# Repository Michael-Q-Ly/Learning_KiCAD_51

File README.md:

# Learning KiCAD 5.1

This repo is made for me to learn how to make my own PCBs using KiCAD 5.1

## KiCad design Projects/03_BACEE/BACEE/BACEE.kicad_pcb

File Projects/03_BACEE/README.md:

# Project 3: BACEE
- - - -
This repository contains the PCB design project from the book and course "[Kicad Like a Pro](https://techexplorations.com/so/kicada/)"

This project implements an Arduino-compatible board mostly using SMD components, and
I will be following Dr. Peter Dalmaris' online instruction to design this board.

The board will contain a micro controller, two EEPROM modules, a clock and calendar
module, two crystal oscillators, and several SMD-sized resistors, capacitors and LEDs.
In addition, it will include headers for connecting peripherals to the micro controller.

The name given to this board is BACEE because it is a "Battery-powered Arduino
with Clock and Extended EEPROM."

This project will combine concepts I learned from the previous two projects

## Learning Objectives
- - - -
1. [x] Explore Kicad's more powerful features such as splitting schematic diagrams into more than one sheet
2. [x] Use an external autorouter
3. [x] Convert a two-layer board into a four-layer board

### How to use the FreeRouting with LayoutEditor
To use [FreeRouting](https://freerouting.org/), you may choose to install it by itself, or with LayoutEditor, which comes with FreeRouting. I chose to install LayoutEditor.

To use FreeRouting, I copied the *freeRouting.jar* file into my project directory. I then exported a spectra design file from Kicad's Pcbnew window.
Next, I ran the following in the command line, (make sure you are referring to the correct directory!):

	$java -jar freeRouting.jar

This opened up a new window to allow me to select the spectra design file. I chose whichever spectra file I needed, and then ran autorouting.

After autorouting finished, I simply imported the spectra session into Pcbnew and verified the routing using a DRC.
That's it!

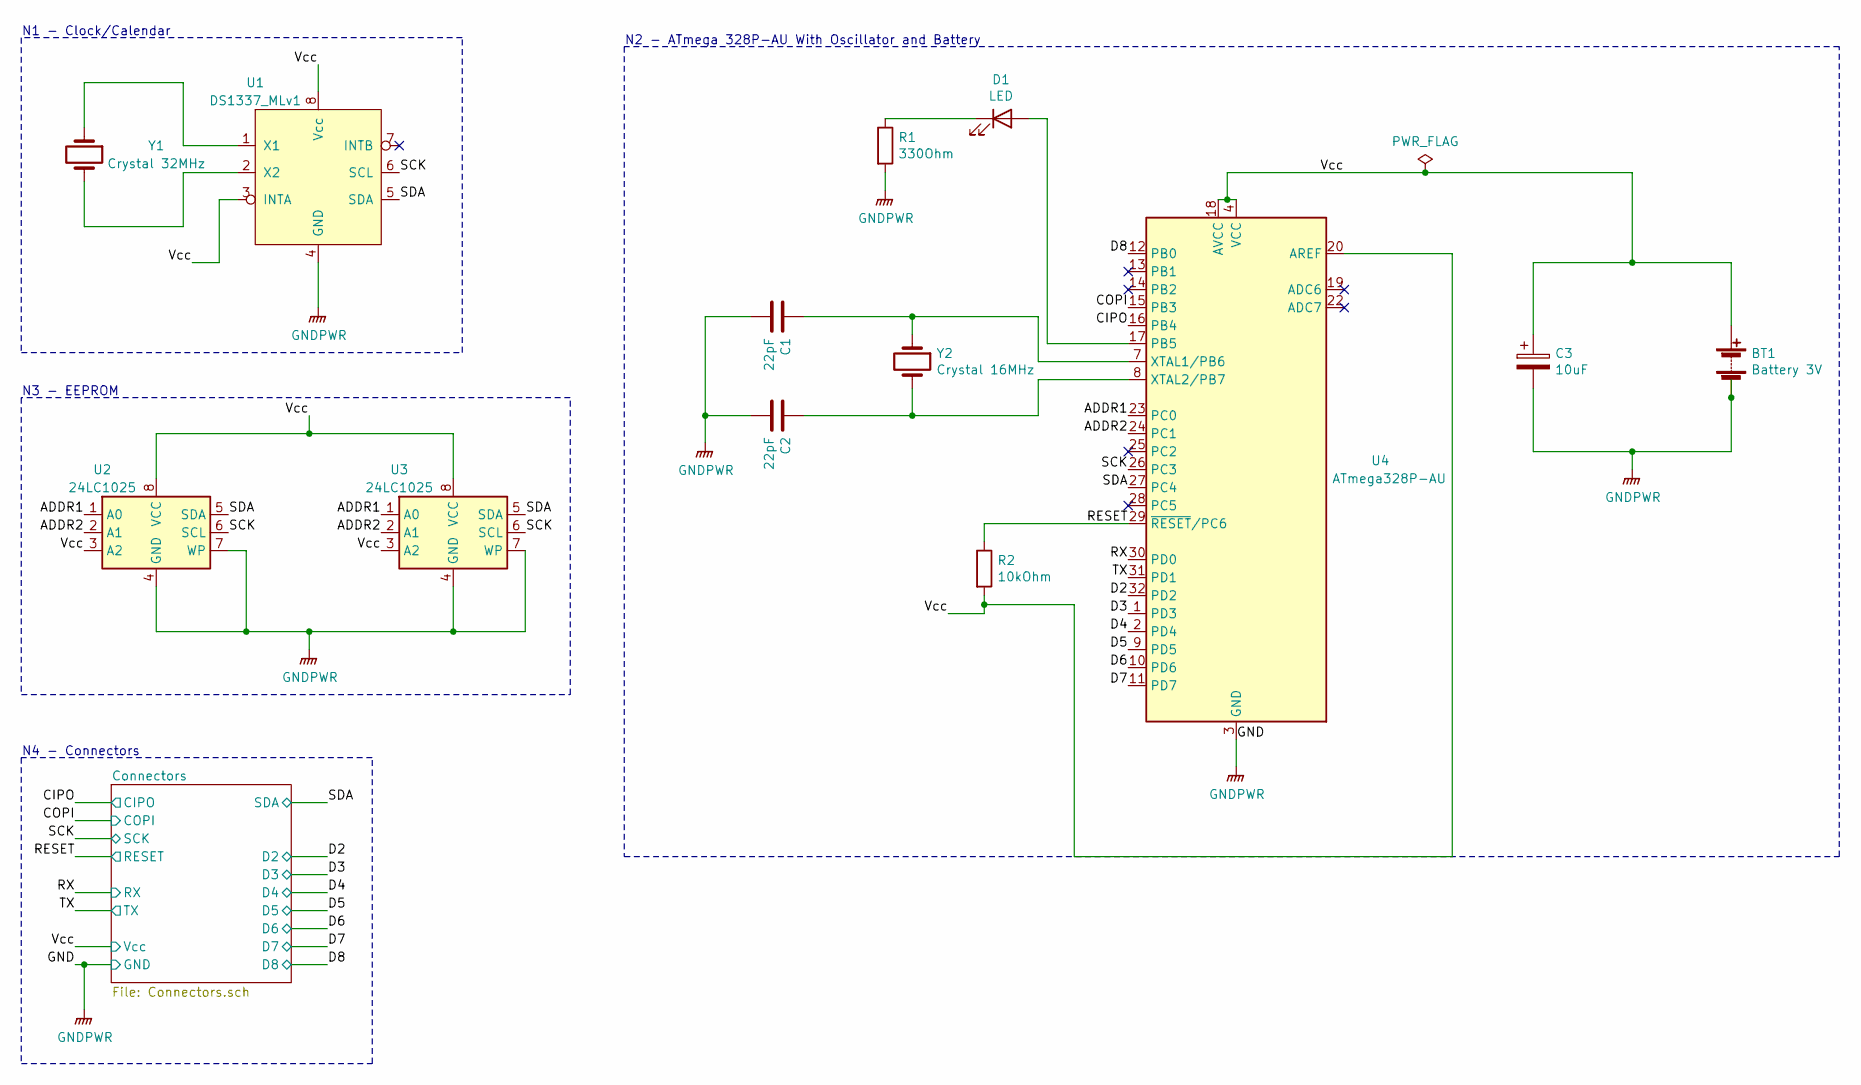
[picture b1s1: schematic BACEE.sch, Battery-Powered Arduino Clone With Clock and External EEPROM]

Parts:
BT1: Battery 3V; PinHeader_1x02_P2.54mm_Vertical
C1, C2: 22pF; D_0805_2012Metric_Pad1.15x1.40mm_HandSolder
C3: 10uF; D_0805_2012Metric_Pad1.15x1.40mm_HandSolder
D1: LED; LED_0805_2012Metric_Pad1.15x1.40mm_HandSolder
R1: 330Ohm; R_0805_2012Metric_Pad1.20x1.40mm_HandSolder
R2: 10kOhm; R_0805_2012Metric_Pad1.20x1.40mm_HandSolder
U1: DS1337_MLv1; SO-8_5.3x6.2mm_P1.27mm
U2, U3: 24LC1025; SOIJ-8_5.3x5.3mm_P1.27mm
U4: ATmega328P-AU; TQFP-32_7x7mm_P0.8mm
Y1: Crystal 32MHz; Crystal_SMD_MicroCrystal_CC7V-T1A-2Pin_3.2x1.5mm
Y2: Crystal 16MHz; Crystal_SMD_5032-2Pin_5.0x3.2mm_HandSoldering

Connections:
/ADDR1: U2.1 (A0), U3.1 (A0), U4.23 (PC0)
/ADDR2: U2.2 (A1), U3.2 (A1), U4.24 (PC1)
/CIPO: U4.16 (PB4); also elsewhere on the board
/COPI: U4.15 (PB3); also elsewhere on the board
/D2: U4.32 (PD2); also elsewhere on the board
/D3: U4.1 (PD3); also elsewhere on the board
/D4: U4.2 (PD4); also elsewhere on the board
/D5: U4.9 (PD5); also elsewhere on the board
/D6: U4.10 (PD6); also elsewhere on the board
/D7: U4.11 (PD7); also elsewhere on the board
/D8: U4.12 (PB0); also elsewhere on the board
/RESET: R2.1, U4.29 (~RESET~/PC6); also elsewhere on the board
/RX: U4.30 (PD0); also elsewhere on the board
/SCK: U1.6 (SCL), U2.6 (SCL), U3.6 (SCL), U4.26 (PC3); also elsewhere on the board
/SDA: U1.5 (SDA), U2.5 (SDA), U3.5 (SDA), U4.27 (PC4); also elsewhere on the board
/TX: U4.31 (PD1); also elsewhere on the board
/Vcc: BT1.1 (+), C3.1, R2.2, U1.3 (INTA), U1.8 (Vcc), U2.3 (A2), U2.8 (VCC), U3.3 (A2), U3.8 (VCC), U4.4 (VCC), U4.6 (VCC), U4.18 (AVCC), U4.20 (AREF); also elsewhere on the board
GNDPWR: BT1.2 (-), C1.2, C2.2, C3.2, R1.2, U1.4 (GND), U2.4 (GND), U2.7 (WP), U3.4 (GND), U3.7 (WP), U4.3 (GND), U4.5 (GND), U4.21 (GND); also elsewhere on the board
unnamed: C1.1, U4.7 (XTAL1/PB6), Y2.1
unnamed: C2.1, U4.8 (XTAL2/PB7), Y2.2
unnamed: D1.1 (K), R1.1
unnamed: D1.2 (A), U4.17 (PB5)
unnamed: U1.1 (X1), Y1.1
unnamed: U1.2 (X2), Y1.2

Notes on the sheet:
N1 - Clock/Calendar
N3 - EEPROM
N2 - ATmega 328P-AU With Oscillator and Battery
N4 - Connectors

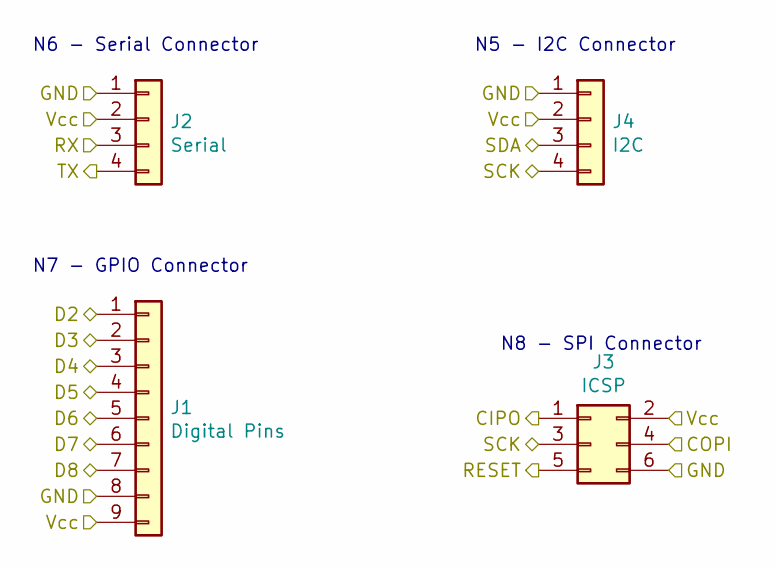
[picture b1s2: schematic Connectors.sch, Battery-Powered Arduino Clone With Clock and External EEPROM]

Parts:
J1: Digital Pins; PinSocket_1x09_P2.54mm_Vertical
J2: Serial; PinSocket_1x04_P2.54mm_Vertical
J3: ICSP; PinSocket_2x03_P2.54mm_Vertical
J4: I2C; PinSocket_1x04_P2.54mm_Vertical

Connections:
/CIPO: J3.1; also elsewhere on the board
/COPI: J3.4; also elsewhere on the board
/D2: J1.1; also elsewhere on the board
/D3: J1.2; also elsewhere on the board
/D4: J1.3; also elsewhere on the board
/D5: J1.4; also elsewhere on the board
/D6: J1.5; also elsewhere on the board
/D7: J1.6; also elsewhere on the board
/D8: J1.7; also elsewhere on the board
/RESET: J3.5; also elsewhere on the board
/RX: J2.3; also elsewhere on the board
/SCK: J3.3, J4.4; also elsewhere on the board
/SDA: J4.3; also elsewhere on the board
/TX: J2.4; also elsewhere on the board
/Vcc: J1.9, J2.2, J3.2, J4.2; also elsewhere on the board
GNDPWR: J1.8, J2.1, J3.6, J4.1; also elsewhere on the board

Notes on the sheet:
N6 - Serial Connector
N5 - I2C Connector
N7 - GPIO Connector
N8 - SPI Connector

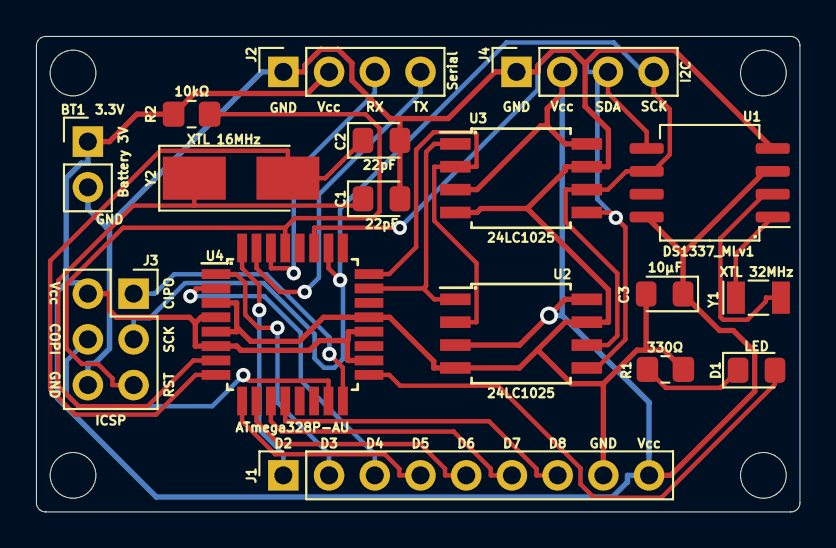
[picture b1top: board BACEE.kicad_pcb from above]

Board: 2 copper layers, 42.4 x 26.4 mm, 17 parts (0 on the bottom side), 24 nets.

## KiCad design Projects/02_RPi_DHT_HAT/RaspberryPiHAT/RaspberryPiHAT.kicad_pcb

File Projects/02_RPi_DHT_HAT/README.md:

# Project 2: Raspberry Pi Full Stack HAT
- - - -
This repository contains the PCB design project from the book and course "[Kicad Like a Pro](https://techexplorations.com/so/kicada/)"

this project implements a Raspberry Pi HAT for a DHT22 temperature and humidity sensor.

## Learning Objectives
- - - -
1. [x] Add surface-mounted devices (SMD) to your board
2. [x] Minimize the amount of space needed for a board
3. [x] Create non-rectangular shapes for the board outline
4. [x] Add mounting holes
5. [x] Revice the board outline after you place the footprints in order to conserve space

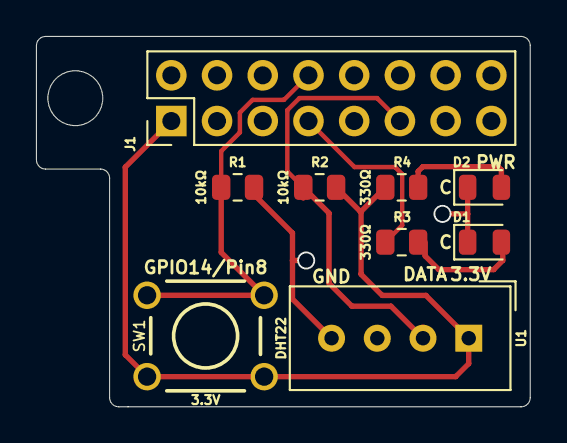
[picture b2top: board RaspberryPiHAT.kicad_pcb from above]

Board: 2 copper layers, 27.4 x 20.6 mm, 9 parts (0 on the bottom side), 7 nets.

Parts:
D1, D2: D; LED_0805_2012Metric
J1: Raspberry_Pi_2_3; PinHeader_2x08_P2.54mm_Vertical
R1, R2: 10kΩ; R_0805_2012Metric
R3, R4: 330Ω; R_0805_2012Metric
SW1: SW_DPST; SW_PUSHBUTTON_PTH
U1: DHT22; Aosong_DHT11_5.5x12.0_P2.54mm

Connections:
/3V3: J1.1, R2.2, R4.1, SW1.1, U1.1
/button_input: J1.8, R1.1, SW1.2
GND: D1.1, D2.1, J1.6, J1.9, R1.2, U1.4
unnamed: D1.2, R3.2
unnamed: D2.2, R4.2
unnamed: J1.7, R3.1
unnamed: J1.11, R2.1, U1.2

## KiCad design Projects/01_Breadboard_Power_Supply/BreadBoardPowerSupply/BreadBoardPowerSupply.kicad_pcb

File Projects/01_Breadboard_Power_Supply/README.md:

# Project 1: Breadboard Power Supply

This is the first project from the book and video course [Kicad Like a Pro](https://techexplorations.com/so/kicada/), by Dr. Peter Dalmaris. It implements a simple breadboard power supply.

In this project, I follow Dr. Dalmaris's videos to create a double-sided PCB for a 5V power supply.
I will be learning the following by the end of this project:
1. [x] How to design a schematic of your board in Eeschema
2. [x] How to design a layout for your board with externally-imposed physical restrictions
3. [x] How to take measurements that relate to the board’s mechanical specifications and used them to design the board outline
4. [x] How to apply the linear schematic design workflow in a real project
5. [x] How to apply the linear layout design workflow in a real project
6. [x] How to select symbols from the library, and associate them with footprints
7. [x] How to manually route the board
8. [x] How to manufacture the board using an online manufacturer

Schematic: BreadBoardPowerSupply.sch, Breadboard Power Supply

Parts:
C1: 470 μF; CP_Radial_D10.0mm_P5.00mm
C2: 47 μF; CP_Radial_D6.3mm_P2.50mm
D1, D2, D3, D4: 1N4007; D_DO-41_SOD81_P10.16mm_Horizontal
D5, D6: LED; LED_D5.0mm
J1: Barrel_Jack_Switch; BarrelJack_CUI_PJ-102AH_Horizontal
J2, J3: Conn_02x02_Odd_Even; PinHeader_2x02_P2.54mm_Vertical
R1, R2: 560 Ω; R_Axial_DIN0207_L6.3mm_D2.5mm_P7.62mm_Horizontal
SW1: SW_DPDT_x2; Switch_Slide_11.6x4mm_EG1218
U1: LM7805_TO220; TO-220-3_Vertical

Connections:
/V-: C1.2, C2.2, D2.2 (A), D4.2 (A), D5.1 (K), D6.1 (K), J2.3, J2.4, J3.3, J3.4, U1.2 (GND)
/Vin: C1.1, D1.1 (K), D3.1 (K), U1.1 (VI)
/Vout1: C2.1, R1.2, SW1.2 (B), U1.3 (VO)
/Vout2: J2.1, J2.2, J3.1, J3.2, R2.1, SW1.1 (A)
unnamed: D1.2 (A), D2.1 (K), J1.1
unnamed: D3.2 (A), D4.1 (K), J1.2
unnamed: D5.2 (A), R1.1
unnamed: D6.2 (A), R2.2

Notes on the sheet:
N1 - Power Input
N2 - Bridge Rectifier
N3 - Voltage Regulator
N4 - Input Power Indicator
N6 - Output Power Indicator
N5 - ON/OFF Switch
N7 - Power Output

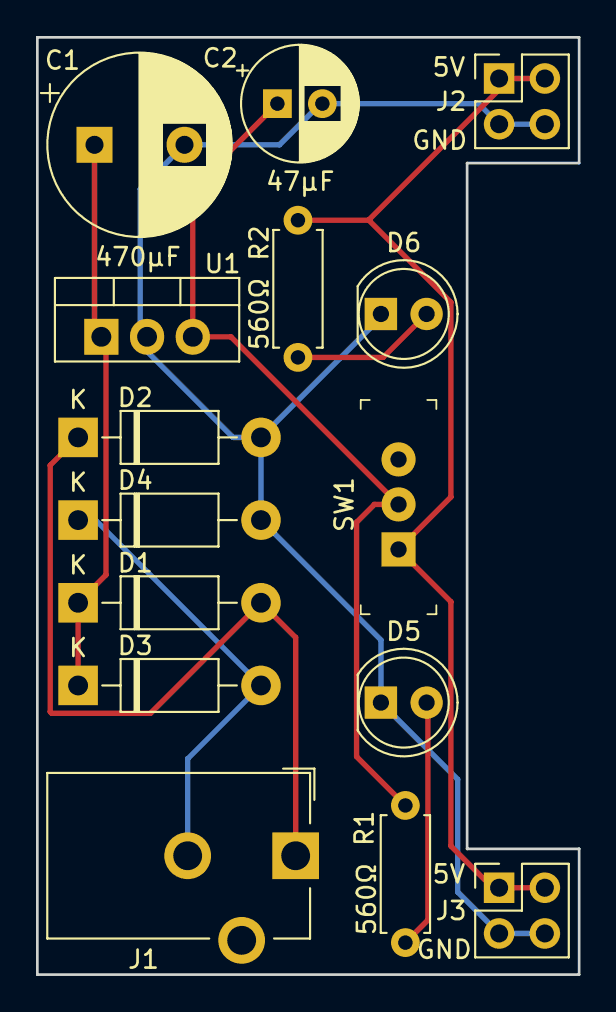
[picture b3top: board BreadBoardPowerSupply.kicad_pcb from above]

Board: 2 copper layers, 30.1 x 52.1 mm, 15 parts (0 on the bottom side), 8 nets.

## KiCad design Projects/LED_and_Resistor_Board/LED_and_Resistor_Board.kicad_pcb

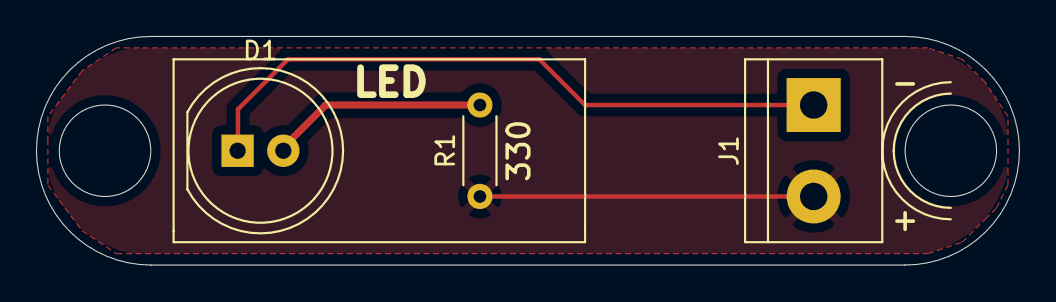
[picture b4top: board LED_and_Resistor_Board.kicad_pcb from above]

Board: 2 copper layers, 54.6 x 12.7 mm, 3 parts (0 on the bottom side), 3 nets.

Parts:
D1: LED; LED_D8.0mm
J1: Conn_01x02_Male; TerminalBlock_bornier-2_P5.08mm
R1: R; R_Axial_DIN0204_L3.6mm_D1.6mm_P5.08mm_Horizontal

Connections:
+5V: J1.2, R1.1
GND: D1.1, J1.1
unnamed: D1.2, R1.2

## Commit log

2021-12-26 First commit - README and .gitignore for KiCAD files added
2021-12-27 Create first project - LED and Resistor Board
2021-12-27 Finish LED_and_Resistor_Board schematic and ERC
2021-12-27 Complete symbol and footprint associations for LED and resistor
2021-12-27 Add THT netlist for LED_and_Resistor_Board profile
2021-12-27 Route LED and resistor and add temrinal block
2021-12-27 Round PCB edges and add mounting holes
2021-12-27 Fill F.Cu layer - 5V, thermal reliefs
2021-12-27 Add silkscreen print and dimensions
2021-12-27 Export image of PCB with dimensions
2021-12-28 Add header to Schematic and change PCB - no more DRC errors
2021-12-29 Begin BreadBoardPowerSupply Eeschema
2021-12-29 Add parts from parts.txt to Eeschema
2021-12-29 Add parts from parts.md to Eeschema
2021-12-29 Arrange and annotate Eeschema
2021-12-29 Assign footprints to all but slide switch - the slide switch likely requires a third party library!
2021-12-29 Add digikey and freetronics symbol and footprint libraries
2021-12-29 Associate slide switch footprint with switch from digikey library
2021-12-29 Wire Eeschema and run ERC
2021-12-30 Add netlist names and rerun Eeschema
2021-12-30 Add comments/text information about the circuit in the Eeschema
2021-12-30 Create a TH netlist for the breadboard power supply
2021-12-30 Finish PCB layout setup - Page settings - Set grid: 1.2700 mm - Set layers: 2-layer - Import Netlist - Set Design Rules: Default + extra track and via dimensions + PWR net class
2021-12-30 Define size and shape of PCB edgecut layer
2021-12-30 Place components on board: - Arrange user interface components - Arrange in functional blocks - Complete placement
2021-12-31 Connect all V- traces on B.Cu
2021-12-31 Connect Vin traces on F.Cu and fix placement to allow traces to go along eges of board
2021-12-31 Run DRC and fix unconnected items: - D2 unconnected V- B.Cu - C1 unconnected Vin F.Cu
2021-12-31 Rotate R2 to shorten wire length of F.Cu and finish routing
2021-12-31 Add copper fill on B.Cu and run DRC: - V- only - Add thermal reliefs
2021-12-31 Add silkscreen text and graphics: - Describe pads - Board version - Logos - Other Instructions - Added a PNG image of the 3=D PCB - Fixed Eeschema capacitors - C1 and C2 needed to their values swapped
2021-12-31 Run DRC and fix errors - ignore courtyard errors for logos and graphics
2021-12-31 Create Gerber files: - Verify Gerber Files - Upload Gerbers to Manufacturer
2021-12-31 Update learning objectives
2021-12-31 Update parts list
2021-12-31 Fix typo in parts.md for capacitor units
2021-12-31 Begin second project and add README.md: Raspberry Pi DHT22 HAT
2021-12-31 Create parts list for RPi HAT
2021-12-31 Rename project directories so that they are numbered
2021-12-31 Finish Project 2 set up
2021-12-31 Project 2: Add symbols from parts.md to Eeschema
2021-12-31 Project 2: Arrange, annotate, and associate Eeschema with footprints
2021-12-31 Project 2: Wire signals and power (PWR_FLAG)
2021-12-31 Project 2: Clean up schematic by adding common GND symbols instead of several PWR_FLAG symbols
2021-12-31 Project 2: Clean up schematic by using net labels for power, ground, and button_input
2021-12-31 Project 2: Add a power LED indicator to the schematic
2021-12-31 Project 2: Add comments on schematic
2021-12-31 Project 2: Run ERC and generate netlist
2021-12-31 Project 2: Edit Pcbnew page settings, grid, layers, netlist, and design rules
2021-12-31 Project 2: Create PCB outline and mounting hole
2021-12-31 Project 2: Place components on board and round PCB edges
2022-01-01 Project 2: Edit footprint from socket to header for RPi in Eeschema
2022-01-01 Project 2: Route nets, critical traces, and power
2022-01-01 Project 2: Reroute nets and add copper fill for GND plane
2022-01-01 Project 2: Add silkscreen text and graphics and generate gerber and drill files
2022-01-01 Project 2: Add board dimensions and 3-D Picture
2022-01-01 Rerun DRC, replot Gerbers, and regenerate drill files
2022-01-01 Project 2: Update learning goals
2022-01-02 Project 3: Create README.md file for Battery-powered Arduino with Clock and extended EEPROM
2022-01-02 Project 3: Create Kicad project files
2022-01-02 Project 3: Set up the title block in the schematic sheet
2022-01-02 Project 3: Create parts list
2022-01-02 Create new child sheet and added project symbols
2022-01-02 Project 3: Add symbol for Atmega328P-AU onto schematic
2022-01-02 Project 3: Download datasheet for DS1337 I2C Serial RTC for custom symbol
2022-01-03 Project 3: Add clock IC custom symbol
2022-01-03 Project 3: Add another item to parts list/schematic - two 2-pin crystals
2022-01-03 Project 3: Arrange symbols
2022-01-03 Project 3: Annotate schematic
2022-01-03 Project 3: Associate footprints
2022-01-03 Project 3: Complete associations and add component values
2022-01-03 Project 3: Complete wiring of connectors hierarchical sheet
2022-01-03 Project 3: Add ATmega 328 datasheet to project directory
2022-01-03 Project 3: Finish wiring and naming nets in root sheet
2022-01-03 Project 3: Add functional block descriptions and generate netlist
2022-01-03 Project 3: Set up Pcbnew description/title block
2022-01-04 Project 3: Edit schematic by changing AREF to Vcc
2022-01-04 Project 3: Set design rules
2022-01-04 Project 3: Complete placement of footprints
2022-01-04 Project 3: Create outline and mounting holes and rearrange U2 and U3
2022-01-04 Project 3: Place footprints closer together
2022-01-04 Project 3: Fully route 4-layer board
2022-01-04 Project 3: Rearrange board components closer and align headers for 4-layer board
2022-01-04 Project 3: Route 4-layer board again
2022-01-04 Project 3: Add 4-layer board PCB as separate file and add copper fill for In2.Cu
2022-01-04 Project3: Set design rules for 2-layer board
2022-01-04 Project 3: Create copper fille for 2-layer board
2022-01-04 Project 3: Add silkscreen text describing the PCB hardware
2022-01-04 Project 3: Add graphics and board description on B.SilkS
2022-01-04 Project 3: Add board measurements and save 3-D image
2022-01-05 Project 3: Run DRC and generate Gerber and Drill files for manufacturing
2022-01-05 Project 3: Update learning objectives
2022-01-05 Project 3: Add top and bottom images of PCB from OSH Park
2022-01-05 Project 3: Add a new bmp file for custom graphics
2022-01-05 Project 3: Add new Ducky_Logo graphic footprint on B.SilkS
2022-01-05 Project 3: Add polarity markers on PCB for ICs and run DRC
2022-01-05 Project 3: Regenerate Gerber and Drill files and verify them for manufacture
2022-01-06 Project 3: Add explanation of how to run FreeRouting to autoroute boards
2022-01-06 Project 3: Add notes on how to import FreeRouting's spectra session into Kicad Pcbnew
